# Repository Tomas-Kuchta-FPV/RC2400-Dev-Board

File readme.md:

# AN026 Dev/breakout Board

Development board for [AN026](https://radiocrafts.com/uploads/AN026_One_Common_Footprint_For_Many_Technologies.pdf). Which is a footprint for Radio Crafts modules.

I created this dev board because I couldn't find any existing development boards for the RC2400 module.  
I believe the community should benefit from my work, which is why I made it universal (AN026) and single-sided.  

> ⚠️ **Work in Progress**

## Features

- PCB antenna. *The traces aren't tuned*
- All pins broken out.
- Its compatible with older modules which doesnt have the newer numbering.

## License

**CERN-OHL-S** [(OSI Approved OSHW License)](https://opensource.org/license/cern-ohl-s)

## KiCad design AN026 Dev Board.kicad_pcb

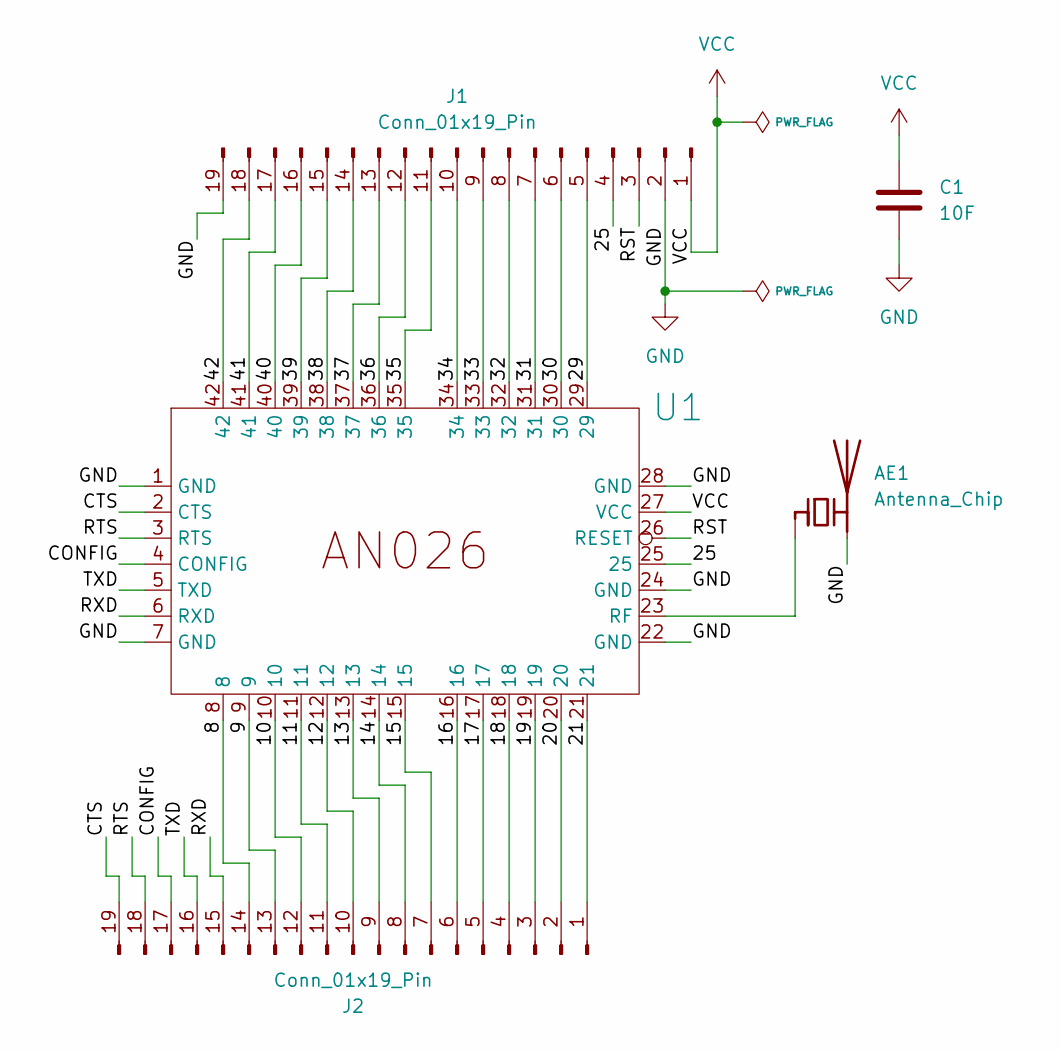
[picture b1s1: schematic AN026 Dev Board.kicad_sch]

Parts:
AE1: Antenna_Chip; Texas_SWRA117D_2.4GHz_Left
C1: 10F; C_0805_2012Metric_Pad1.18x1.45mm_HandSolder
J1, J2: Conn_01x19_Pin; PinHeader_1x19_P2.54mm_Vertical
U1: AN026

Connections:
/8: J2.14, U1.8
/9: J2.13, U1.9
/10: J2.12, U1.10
/11: J2.11, U1.11
/12: J2.10, U1.12
/13: J2.9, U1.13
/14: J2.8, U1.14
/15: J2.7, U1.15
/16: J2.6, U1.16
/17: J2.5, U1.17
/18: J2.4, U1.18
/19: J2.3, U1.19
/20: J2.2, U1.20
/21: J2.1, U1.21
/25: J1.4, U1.25
/29: J1.5, U1.29
/30: J1.6, U1.30
/31: J1.7, U1.31
/32: J1.8, U1.32
/33: J1.9, U1.33
/34: J1.10, U1.34
/35: J1.11, U1.35
/36: J1.12, U1.36
/37: J1.13, U1.37
/38: J1.14, U1.38
/39: J1.15, U1.39
/40: J1.16, U1.40
/41: J1.17, U1.41
/42: J1.18, U1.42
/CONFIG: J2.17, U1.4 (CONFIG)
/CTS: J2.19, U1.2 (CTS)
/RST: J1.3, U1.26 (RESET)
/RTS: J2.18, U1.3 (RTS)
/RXD: J2.15, U1.6 (RXD)
/TXD: J2.16, U1.5 (TXD)
GND: AE1.2 (PCB_Trace), C1.2, J1.2, J1.19, U1.1 (GND), U1.7 (GND), U1.22 (GND), U1.24 (GND), U1.28 (GND)
unnamed: AE1.1 (FEED), U1.23 (RF)
VCC: C1.1, J1.1, U1.27 (VCC)

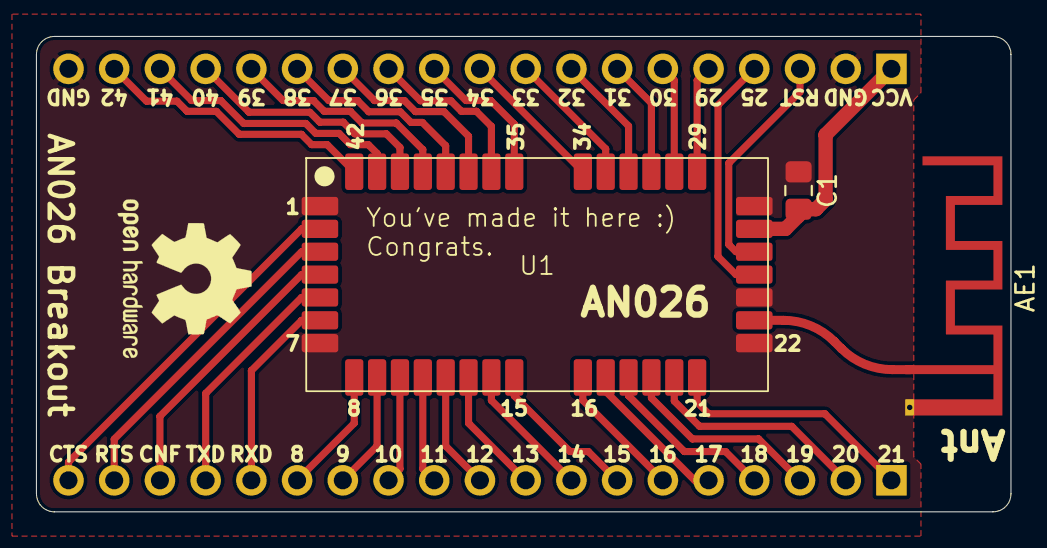
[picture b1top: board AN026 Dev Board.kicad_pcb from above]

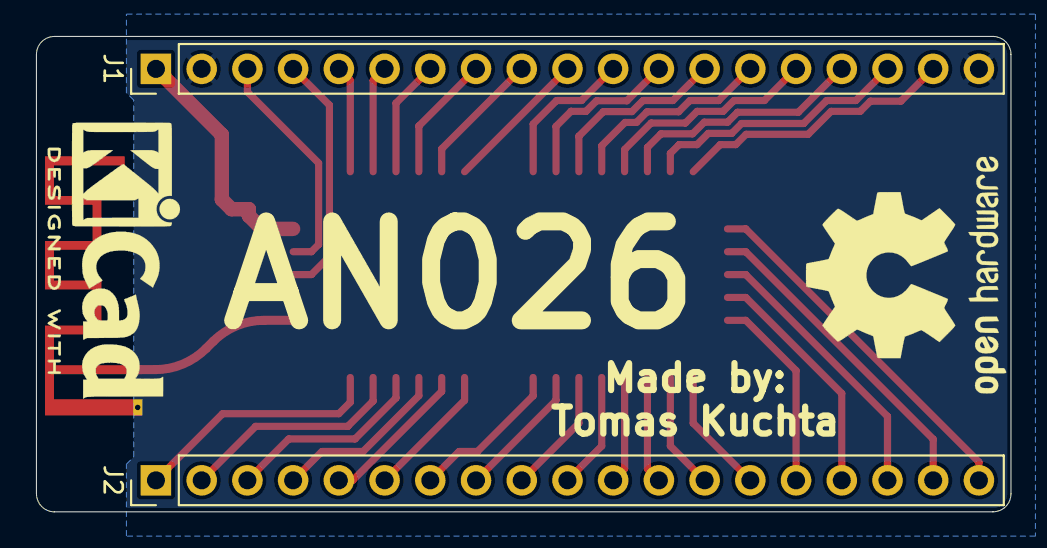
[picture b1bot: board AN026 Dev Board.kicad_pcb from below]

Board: 2 copper layers, 54.1 x 26.4 mm, 5 parts (2 on the bottom side), 38 nets.

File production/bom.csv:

Designator,Footprint,Quantity,Value,LCSC Part #
AE1,Texas_SWRA117D_2.4GHz_Left,1,Antenna_Chip,
C1,0805,1,10F,
"J1, J2",PinHeader_1x19_P2.54mm_Vertical,2,Conn_01x19_Pin,
U1,AN026,1,~,

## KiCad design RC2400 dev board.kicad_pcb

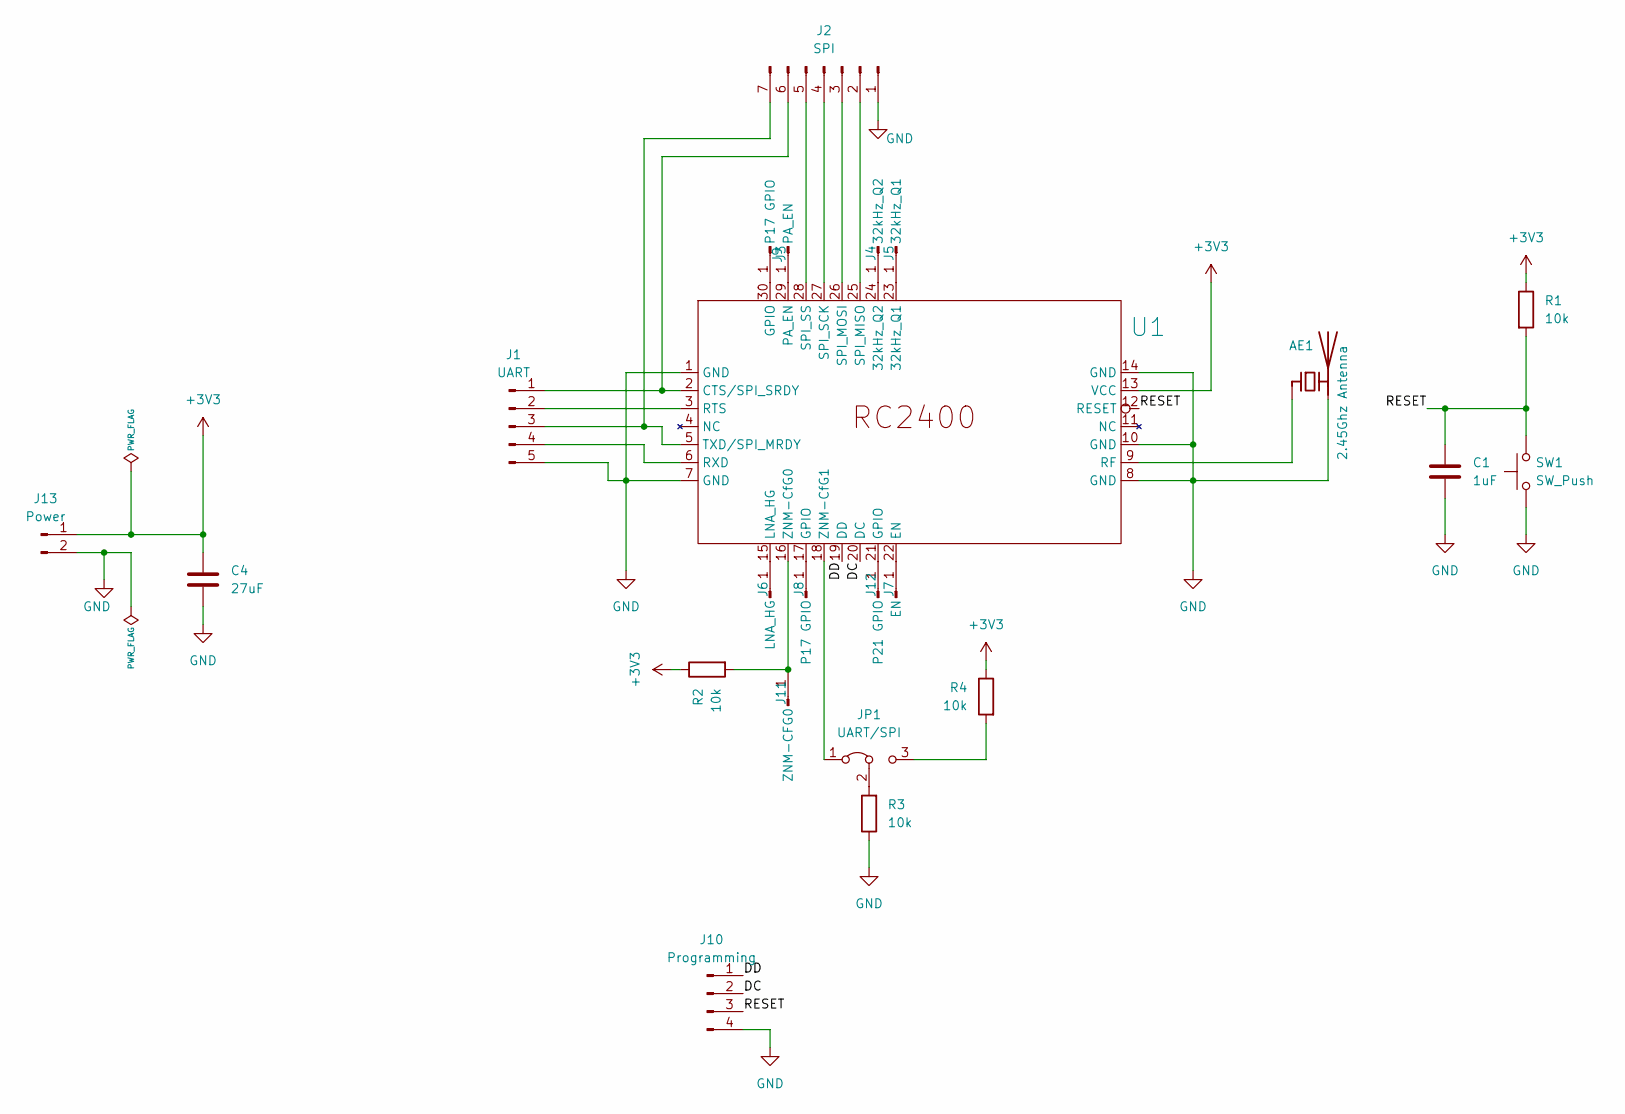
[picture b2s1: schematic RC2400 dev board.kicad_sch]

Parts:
AE1: 2.45Ghz Antenna; Texas_SWRA117D_2.4GHz_Right
C1: 1uF; C_1206_3216Metric_Pad1.33x1.80mm_HandSolder
C4: 27uF; C_1206_3216Metric_Pad1.33x1.80mm_HandSolder
J1: UART; PinHeader_1x05_P2.54mm_Vertical
J2: SPI; PinHeader_1x07_P2.54mm_Vertical
J3: PA_EN; TestPoint_Pad_1.5x1.5mm
J4: 32kHz_Q2; TestPoint_Pad_1.5x1.5mm
J5: 32kHz_Q1; TestPoint_Pad_1.5x1.5mm
J6: LNA_HG; TestPoint_Pad_1.5x1.5mm
J7: EN; TestPoint_Pad_1.5x1.5mm
J8, J9: P17 GPIO; TestPoint_Pad_1.5x1.5mm
J10: Programming; PinHeader_1x04_P2.54mm_Vertical
J11: ZNM-CFG0; TestPoint_Pad_1.5x1.5mm
J12: P21 GPIO; TestPoint_Pad_1.5x1.5mm
J13: Power; PinHeader_1x02_P2.54mm_Vertical
JP1: UART/SPI; PinHeader_1x03_P2.54mm_Vertical
R1, R2, R3, R4: 10k; R_1206_3216Metric_Pad1.30x1.75mm_HandSolder
SW1: SW_Push; PinHeader_1x02_P2.54mm_Vertical
U1: RC2400

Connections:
+3V3: C4.1, J13.1, R1.1, R2.1, R4.1, U1.13 (VCC)
/DC: J10.2, U1.20 (DC)
/DD: J10.1, U1.19 (DD)
/RESET: C1.1, J10.3, R1.2, SW1.2, U1.12 (RESET)
GND: AE1.2 (PCB_Trace), C1.2, C4.2, J1.5, J2.1, J10.4, J13.2, R3.1, SW1.1, U1.1 (GND), U1.7 (GND), U1.8 (GND), U1.10 (GND), U1.14 (GND)
unnamed: AE1.1 (FEED), U1.9 (RF)
unnamed: J1.1, J2.6, U1.2 (CTS/SPI_SRDY)
unnamed: J1.2, U1.3 (RTS)
unnamed: J1.3, J2.7, U1.5 (TXD/SPI_MRDY)
unnamed: J1.4, U1.6 (RXD)
unnamed: J2.2, U1.25 (SPI_MISO)
unnamed: J2.3, U1.26 (SPI_MOSI)
unnamed: J2.4, U1.27 (SPI_SCK)
unnamed: J2.5, U1.28 (SPI_SS)
unnamed: J3.1, U1.29 (PA_EN)
unnamed: J4.1, U1.24 (32kHz_Q2)
unnamed: J5.1, U1.23 (32kHz_Q1)
unnamed: J6.1, U1.15 (LNA_HG)
unnamed: J7.1, U1.22 (EN)
unnamed: J8.1, U1.17 (GPIO)
unnamed: J9.1, U1.30 (GPIO)
unnamed: J11.1, R2.2, U1.16 (ZNM-CfG0)
unnamed: J12.1, U1.21 (GPIO)
unnamed: JP1.1 (A), U1.18 (ZNM-CfG1)
unnamed: JP1.3 (B), R4.2
unnamed: JP1.2 (C), R3.2

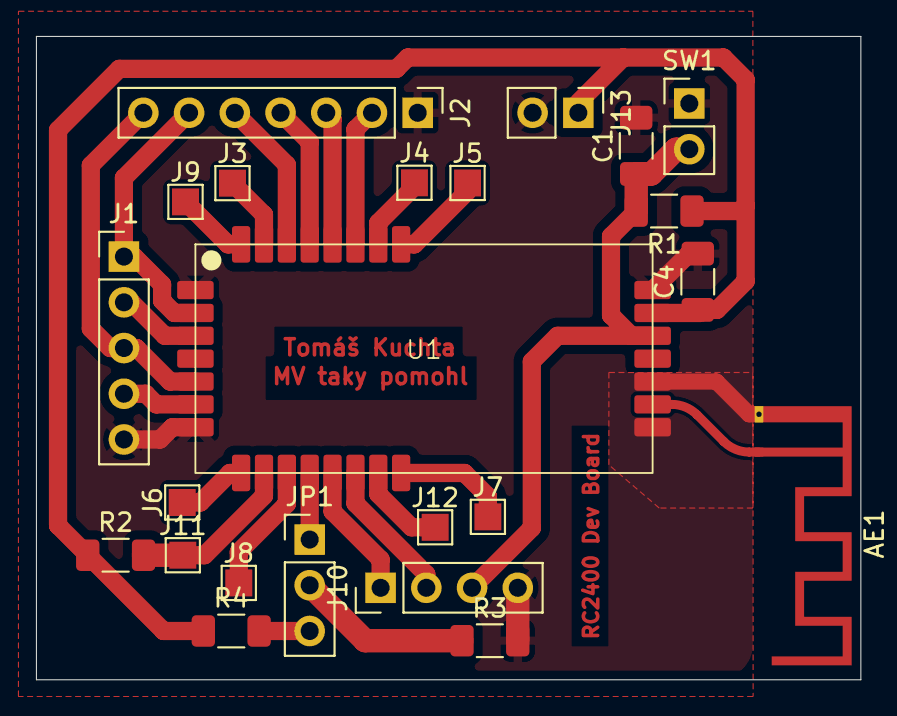
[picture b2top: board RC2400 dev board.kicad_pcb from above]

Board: 2 copper layers, 45.8 x 35.7 mm, 23 parts (0 on the bottom side), 26 nets.

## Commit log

2025-05-18 Initial commit of the project
2025-05-18 added license and readme
2025-09-18 Moving towards the universal AN026 footprint.
    Fixed pad spacing fot the top and bottom sides.
    And moved the pads invards.
2025-09-21 Updated symbols, Made schematic and routed traces.
2025-09-21 Finished up the PCB.
2025-09-21 Added gitignore
2025-09-21 Its AN026 not ANO26.
2025-09-21 Updated readme and saved it from the AI slop.
2025-09-21 Update readme.md - forgor to update the heading
